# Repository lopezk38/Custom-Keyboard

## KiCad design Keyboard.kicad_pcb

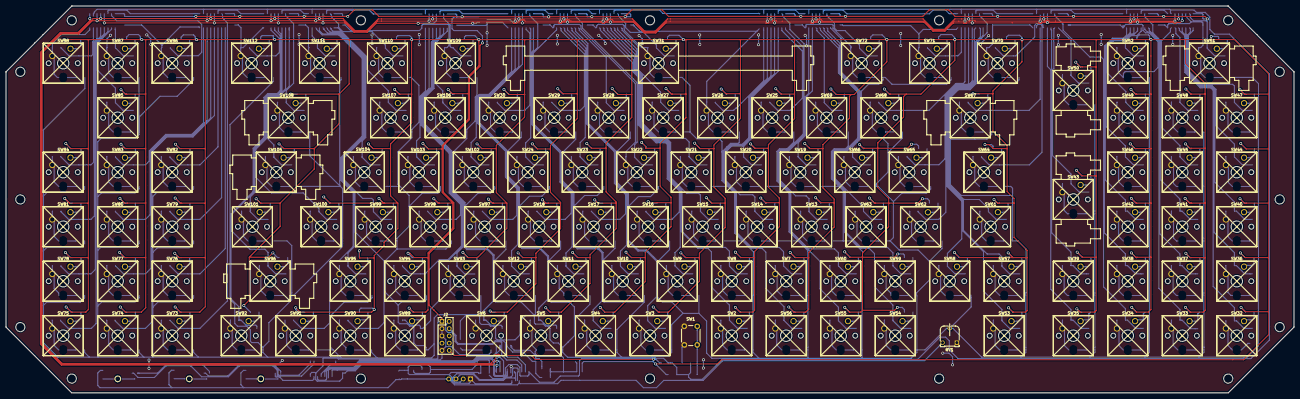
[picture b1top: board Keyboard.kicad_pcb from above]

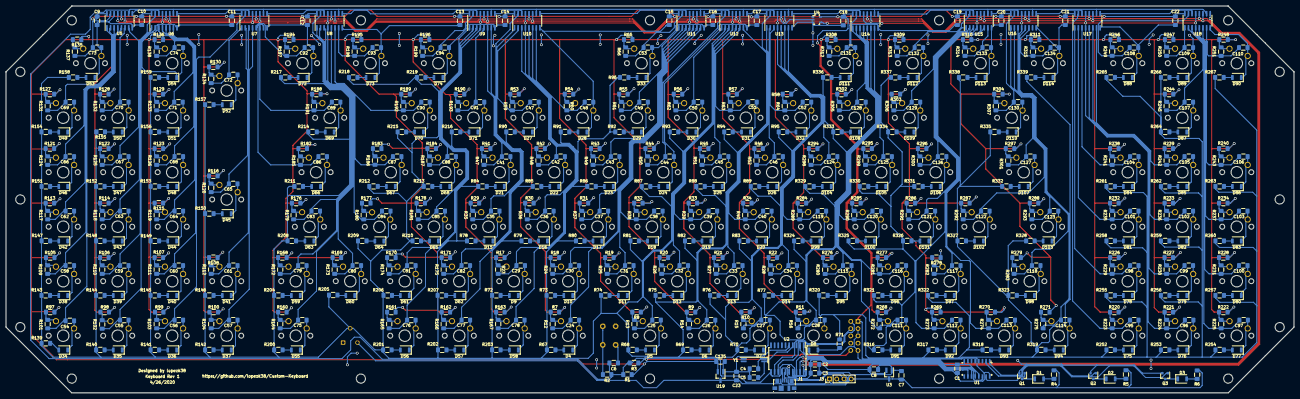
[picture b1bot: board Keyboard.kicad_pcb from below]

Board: 2 copper layers, 450.2 x 135.2 mm, 727 parts (613 on the bottom side), 375 nets.

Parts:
C1, C3: 100n; C_1206_3216Metric_Pad1.42x1.75mm_HandSolder
C2: 4.7u; C_1206_3216Metric_Pad1.42x1.75mm_HandSolder
C4, C5: 8.2p; C_1206_3216Metric_Pad1.42x1.75mm_HandSolder
C6: 4.7n; C_1206_3216Metric_Pad1.42x1.75mm_HandSolder
C7, C8, C23, C135: 1u; C_1206_3216Metric_Pad1.42x1.75mm_HandSolder
C9, C10, C11, C12, C13, C14, C15, C16, C17, C18, C19, C20, C21, C22: 1n; C_1206_3216Metric_Pad1.42x1.75mm_HandSolder
C24, C25, C26, C27, C28, C29, C30, C31, C32, C33, C34, C35, C36, C37, C38, C39, C40, C41, C42, C43, C44, C45, C46, C47, C48, C49, C50, C51, C52, C53, C54, C55, C56, C57, C58, C59, C60, C61, C62, C63, C64, C65, C66, C67, C68, C69, C70, C71, C72, C73, C74, C75, C76, C77, C78, C79, C80, C81, C82, C83, C84, C85, C86, C87, C88, C89, C90, C91, C92, C93, C94, C95, C96, C97, C98, C99, C100, C101, C102, C103, C104, C105, C106, C107, C108, C109, C110, C111, C112, C113, C114, C115, C116, C117, C118, C119, C120, C121, C122, C123, C124, C125, C126, C127, C128, C129, C130, C131, C132, C133, C134: .047u; C_1206_3216Metric_Pad1.42x1.75mm_HandSolder
D1: NUM LOCK; LED_1206_3216Metric_ReverseMount_Hole1.8x2.4mm
D2: CAPS LOCK; LED_1206_3216Metric_ReverseMount_Hole1.8x2.4mm
D3: SCROLL LOCK; LED_1206_3216Metric_ReverseMount_Hole1.8x2.4mm
D4: LED F4; LED_1206_3216Metric_ReverseMount_Hole1.8x2.4mm
D5: LED F5; LED_1206_3216Metric_ReverseMount_Hole1.8x2.4mm
D6: LED F6; LED_1206_3216Metric_ReverseMount_Hole1.8x2.4mm
D7: LED F7; LED_1206_3216Metric_ReverseMount_Hole1.8x2.4mm
D8: LED F8; LED_1206_3216Metric_ReverseMount_Hole1.8x2.4mm
D9, D46: LED 4; LED_1206_3216Metric_ReverseMount_Hole1.8x2.4mm
D10, D47: LED 5; LED_1206_3216Metric_ReverseMount_Hole1.8x2.4mm
D11, D48: LED 6; LED_1206_3216Metric_ReverseMount_Hole1.8x2.4mm
D12, D42: LED 7; LED_1206_3216Metric_ReverseMount_Hole1.8x2.4mm
D13, D43: LED 8; LED_1206_3216Metric_ReverseMount_Hole1.8x2.4mm
D14, D44: LED 9; LED_1206_3216Metric_ReverseMount_Hole1.8x2.4mm
D15: LED E; LED_1206_3216Metric_ReverseMount_Hole1.8x2.4mm
D16: LED R; LED_1206_3216Metric_ReverseMount_Hole1.8x2.4mm
D17: LED T; LED_1206_3216Metric_ReverseMount_Hole1.8x2.4mm
D18: LED Y; LED_1206_3216Metric_ReverseMount_Hole1.8x2.4mm
D19: LED U; LED_1206_3216Metric_ReverseMount_Hole1.8x2.4mm
D20: LED I; LED_1206_3216Metric_ReverseMount_Hole1.8x2.4mm
D21: LED D; LED_1206_3216Metric_ReverseMount_Hole1.8x2.4mm
D22: LED F; LED_1206_3216Metric_ReverseMount_Hole1.8x2.4mm
D23: LED G; LED_1206_3216Metric_ReverseMount_Hole1.8x2.4mm
D24: LED H; LED_1206_3216Metric_ReverseMount_Hole1.8x2.4mm
D25: LED J; LED_1206_3216Metric_ReverseMount_Hole1.8x2.4mm
D26: LED K; LED_1206_3216Metric_ReverseMount_Hole1.8x2.4mm
D27: LED C; LED_1206_3216Metric_ReverseMount_Hole1.8x2.4mm
D28: LED V; LED_1206_3216Metric_ReverseMount_Hole1.8x2.4mm
D29: LED B; LED_1206_3216Metric_ReverseMount_Hole1.8x2.4mm
D30: LED N; LED_1206_3216Metric_ReverseMount_Hole1.8x2.4mm
D31: LED M; LED_1206_3216Metric_ReverseMount_Hole1.8x2.4mm
D32: LED ,; LED_1206_3216Metric_ReverseMount_Hole1.8x2.4mm
D33: LED SPACE; LED_1206_3216Metric_ReverseMount_Hole1.8x2.4mm
D34: LED EXT1; LED_1206_3216Metric_ReverseMount_Hole1.8x2.4mm
D35: LED EXT2; LED_1206_3216Metric_ReverseMount_Hole1.8x2.4mm
D36: LED EXT3; LED_1206_3216Metric_ReverseMount_Hole1.8x2.4mm
D37: LED EXT4; LED_1206_3216Metric_ReverseMount_Hole1.8x2.4mm
D38: LED NUM LOCK; LED_1206_3216Metric_ReverseMount_Hole1.8x2.4mm
D39, D109: LED /; LED_1206_3216Metric_ReverseMount_Hole1.8x2.4mm
D40: LED *; LED_1206_3216Metric_ReverseMount_Hole1.8x2.4mm
D41, D96: LED -; LED_1206_3216Metric_ReverseMount_Hole1.8x2.4mm
D45: LED +; LED_1206_3216Metric_ReverseMount_Hole1.8x2.4mm
D49, D60: LED 1; LED_1206_3216Metric_ReverseMount_Hole1.8x2.4mm
D50, D61: LED 2; LED_1206_3216Metric_ReverseMount_Hole1.8x2.4mm
D51, D62: LED 3; LED_1206_3216Metric_ReverseMount_Hole1.8x2.4mm
D52, D107: LED ENTER; LED_1206_3216Metric_ReverseMount_Hole1.8x2.4mm
D53, D95: LED 0; LED_1206_3216Metric_ReverseMount_Hole1.8x2.4mm
D54, D108: LED .; LED_1206_3216Metric_ReverseMount_Hole1.8x2.4mm
D55: LED ESC; LED_1206_3216Metric_ReverseMount_Hole1.8x2.4mm
D56: LED F1; LED_1206_3216Metric_ReverseMount_Hole1.8x2.4mm
D57: LED F2; LED_1206_3216Metric_ReverseMount_Hole1.8x2.4mm
D58: LED F3; LED_1206_3216Metric_ReverseMount_Hole1.8x2.4mm
D59: LED `; LED_1206_3216Metric_ReverseMount_Hole1.8x2.4mm
D63: LED TAB; LED_1206_3216Metric_ReverseMount_Hole1.8x2.4mm
D64: LED Q; LED_1206_3216Metric_ReverseMount_Hole1.8x2.4mm
D65: LED W; LED_1206_3216Metric_ReverseMount_Hole1.8x2.4mm
D66: LED CAPL; LED_1206_3216Metric_ReverseMount_Hole1.8x2.4mm
D67: LED A; LED_1206_3216Metric_ReverseMount_Hole1.8x2.4mm
D68: LED S; LED_1206_3216Metric_ReverseMount_Hole1.8x2.4mm
D69: LED LSHFT; LED_1206_3216Metric_ReverseMount_Hole1.8x2.4mm
D70: LED Z; LED_1206_3216Metric_ReverseMount_Hole1.8x2.4mm
D71: LED X; LED_1206_3216Metric_ReverseMount_Hole1.8x2.4mm
D72: LED LCTRL; LED_1206_3216Metric_ReverseMount_Hole1.8x2.4mm
D73: LED LWIND; LED_1206_3216Metric_ReverseMount_Hole1.8x2.4mm
D74: LALT; LED_1206_3216Metric_ReverseMount_Hole1.8x2.4mm
D75: LED PRINT SCREEN; LED_1206_3216Metric_ReverseMount_Hole1.8x2.4mm
D76: LED SCROLL LOCK; LED_1206_3216Metric_ReverseMount_Hole1.8x2.4mm
D77: LED PAUSE; LED_1206_3216Metric_ReverseMount_Hole1.8x2.4mm
D78: LED INSERT; LED_1206_3216Metric_ReverseMount_Hole1.8x2.4mm
D79: LED HOME; LED_1206_3216Metric_ReverseMount_Hole1.8x2.4mm
D80: LED PAGE UP; LED_1206_3216Metric_ReverseMount_Hole1.8x2.4mm
D81: LED DELETE; LED_1206_3216Metric_ReverseMount_Hole1.8x2.4mm
D82: LED END; LED_1206_3216Metric_ReverseMount_Hole1.8x2.4mm
D83: LED PAGE DOWN; LED_1206_3216Metric_ReverseMount_Hole1.8x2.4mm
D84: LED EXT8; LED_1206_3216Metric_ReverseMount_Hole1.8x2.4mm
D85: LED EXT9; LED_1206_3216Metric_ReverseMount_Hole1.8x2.4mm
D86: LED EXT10; LED_1206_3216Metric_ReverseMount_Hole1.8x2.4mm
D87: LED UP; LED_1206_3216Metric_ReverseMount_Hole1.8x2.4mm
D88: LED LEFT; LED_1206_3216Metric_ReverseMount_Hole1.8x2.4mm
D89: LED DOWN; LED_1206_3216Metric_ReverseMount_Hole1.8x2.4mm
D90: LED RIGHT; LED_1206_3216Metric_ReverseMount_Hole1.8x2.4mm
D91: LED F9; LED_1206_3216Metric_ReverseMount_Hole1.8x2.4mm
D92: LED F10; LED_1206_3216Metric_ReverseMount_Hole1.8x2.4mm
D93: LED F11; LED_1206_3216Metric_ReverseMount_Hole1.8x2.4mm
D94: LED F12; LED_1206_3216Metric_ReverseMount_Hole1.8x2.4mm
D97: LED =; LED_1206_3216Metric_ReverseMount_Hole1.8x2.4mm
D98: LED BACK; LED_1206_3216Metric_ReverseMount_Hole1.8x2.4mm
D99: LED O; LED_1206_3216Metric_ReverseMount_Hole1.8x2.4mm
D100: LED P; LED_1206_3216Metric_ReverseMount_Hole1.8x2.4mm
D101: LED [; LED_1206_3216Metric_ReverseMount_Hole1.8x2.4mm
D102: LED ]; LED_1206_3216Metric_ReverseMount_Hole1.8x2.4mm
D103: LED \; LED_1206_3216Metric_ReverseMount_Hole1.8x2.4mm
D104: LED L; LED_1206_3216Metric_ReverseMount_Hole1.8x2.4mm
D105: LED ;; LED_1206_3216Metric_ReverseMount_Hole1.8x2.4mm
D106: LED '; LED_1206_3216Metric_ReverseMount_Hole1.8x2.4mm
D110: LED RSHIFT; LED_1206_3216Metric_ReverseMount_Hole1.8x2.4mm
D111: LED RALT; LED_1206_3216Metric_ReverseMount_Hole1.8x2.4mm
D112: LED RWIND; LED_1206_3216Metric_ReverseMount_Hole1.8x2.4mm
D113: LED APP; LED_1206_3216Metric_ReverseMount_Hole1.8x2.4mm
D114: LED RCTRL; LED_1206_3216Metric_ReverseMount_Hole1.8x2.4mm
J1: USB_B_Micro; USB_Micro-B_Molex_47346-0001
J2: DEBUG; PinHeader_2x05_P2.54mm_Vertical
J3: USB; PinHeader_1x04_P2.54mm_Vertical
Q1, Q2, Q3: DMG2302U; SOT-23
R1: 100K; R_1206_3216Metric_Pad1.42x1.75mm_HandSolder
R2, R3: 39; R_1206_3216Metric_Pad1.42x1.75mm_HandSolder
R4, R5, R6, R67, R68, R69, R70, R71, R72, R73, R74, R75, R76, R77, R78, R79, R80, R81, R82, R83, R84, R85, R86, R87, R88, R89, R90, R91, R92, R93, R94, R95, R96, R139, R140, R141, R142, R143, R144, R145, R146, R147, R148, R149, R150, R151, R152, R153, R154, R155, R156, R157, R158, R159, R200, R201, R202, R203, R204, R205, R206, R207, R208, R209, R210, R211, R212, R213, R214, R215, R216, R217, R218, R219, R252, R253, R254, R255, R256, R257, R258, R259, R260, R261, R262, R263, R264, R265, R266, R267, R316, R317, R318, R319, R320, R321, R322, R323, R324, R325, R326, R327, R328, R329, R330, R331, R332, R333, R334, R335, R336, R337, R338, R339: 1.8k; R_1206_3216Metric_Pad1.42x1.75mm_HandSolder
R7, R8, R9, R10, R11, R12, R13, R14, R15, R16, R17, R18, R19, R20, R21, R22, R23, R24, R25, R26, R27, R28, R29, R30, R31, R32, R33, R34, R35, R36, R37, R38, R39, R40, R41, R42, R43, R44, R45, R46, R47, R48, R49, R50, R51, R52, R53, R54, R55, R56, R57, R58, R59, R60, R61, R62, R63, R64, R65, R66, R97, R98, R99, R100, R101, R102, R103, R104, R105, R106, R107, R108, R109, R110, R111, R112, R113, R114, R115, R116, R117, R118, R119, R120, R121, R122, R123, R124, R125, R126, R127, R128, R129, R130, R131, R132, R133, R134, R135, R136, R137, R138, R160, R161, R162, R163, R164, R165, R166, R167, R168, R169, R170, R171, R172, R173, R174, R175, R176, R177, R178, R179, R180, R181, R182, R183, R184, R185, R186, R187, R188, R189, R190, R191, R192, R193, R194, R195, R196, R197, R198, R199, R220, R221, R222, R223, R224, R225, R226, R227, R228, R229, R230, R231, R232, R233, R234, R235, R236, R237, R238, R239, R240, R241, R242, R243, R244, R245, R246, R247, R248, R249, R250, R251, R268, R269, R270, R271, R272, R273, R274, R275, R276, R277, R278, R279, R280, R281, R282, R283, R284, R285, R286, R287, R288, R289, R290, R291, R292, R293, R294, R295, R296, R297, R298, R299, R300, R301, R302, R303, R304, R305, R306, R307, R308, R309, R310, R311, R312, R313, R314, R315: 10k; R_1206_3216Metric_Pad1.42x1.75mm_HandSolder
RV1: R_POT; Potentiometer_Runtron_RM-065_Vertical
SW1: SW_Push; SW_PUSH_6mm
SW2: F4; SW_Cherry_MX_1.00u_PCB
SW3: F5; SW_Cherry_MX_1.00u_PCB
SW4: F6; SW_Cherry_MX_1.00u_PCB
SW5: F7; SW_Cherry_MX_1.00u_PCB
SW6: F8; SW_Cherry_MX_1.00u_PCB
SW7, SW44: 4; SW_Cherry_MX_1.00u_PCB
SW8, SW45: 5; SW_Cherry_MX_1.00u_PCB
SW9, SW46: 6; SW_Cherry_MX_1.00u_PCB
SW10, SW40: 7; SW_Cherry_MX_1.00u_PCB
SW11, SW41: 8; SW_Cherry_MX_1.00u_PCB
SW12, SW42: 9; SW_Cherry_MX_1.00u_PCB
SW13: E; SW_Cherry_MX_1.00u_PCB
SW14: R; SW_Cherry_MX_1.00u_PCB
SW15: T; SW_Cherry_MX_1.00u_PCB
SW16: Y; SW_Cherry_MX_1.00u_PCB
SW17: U; SW_Cherry_MX_1.00u_PCB
SW18: I; SW_Cherry_MX_1.00u_PCB
SW19: D; SW_Cherry_MX_1.00u_PCB
SW20: F; SW_Cherry_MX_1.00u_PCB
SW21: G; SW_Cherry_MX_1.00u_PCB
SW22: H; SW_Cherry_MX_1.00u_PCB
SW23: J; SW_Cherry_MX_1.00u_PCB
SW24: K; SW_Cherry_MX_1.00u_PCB
SW25: C; SW_Cherry_MX_1.00u_PCB
SW26: V; SW_Cherry_MX_1.00u_PCB
SW27: B; SW_Cherry_MX_1.00u_PCB
SW28: N; SW_Cherry_MX_1.00u_PCB
SW29: M; SW_Cherry_MX_1.00u_PCB
SW30: ,; SW_Cherry_MX_1.00u_PCB
SW31: SPACE; SW_Cherry_MX_1.00u_PCB
SW32: EXT1; SW_Cherry_MX_1.00u_PCB
SW33: EXT2; SW_Cherry_MX_1.00u_PCB
SW34: EXT3; SW_Cherry_MX_1.00u_PCB
SW35: EXT4; SW_Cherry_MX_1.00u_PCB
SW36: NUM LOCK; SW_Cherry_MX_1.00u_PCB
SW37, SW107: /; SW_Cherry_MX_1.00u_PCB
SW38: *; SW_Cherry_MX_1.00u_PCB
SW39, SW94: -; SW_Cherry_MX_1.00u_PCB
SW43: +; SW_Cherry_MX_1.00u_PCB
SW47, SW58: 1; SW_Cherry_MX_1.00u_PCB
SW48, SW59: 2; SW_Cherry_MX_1.00u_PCB
SW49, SW60: 3; SW_Cherry_MX_1.00u_PCB
SW50, SW105: ENTER; SW_Cherry_MX_1.00u_PCB
SW51, SW93: 0; SW_Cherry_MX_1.00u_PCB
SW52, SW106: .; SW_Cherry_MX_1.00u_PCB
SW53: ESC; SW_Cherry_MX_1.00u_PCB
SW54: F1; SW_Cherry_MX_1.00u_PCB
SW55: F2; SW_Cherry_MX_1.00u_PCB
SW56: F3; SW_Cherry_MX_1.00u_PCB
SW57: `; SW_Cherry_MX_1.00u_PCB
SW61: TAB; SW_Cherry_MX_1.00u_PCB
SW62: Q; SW_Cherry_MX_1.00u_PCB
SW63: W; SW_Cherry_MX_1.00u_PCB
SW64: CAPL; SW_Cherry_MX_1.00u_PCB
SW65: A; SW_Cherry_MX_1.00u_PCB
SW66: S; SW_Cherry_MX_1.00u_PCB
SW67: LSHFT; SW_Cherry_MX_1.00u_PCB
SW68: Z; SW_Cherry_MX_1.00u_PCB
SW69: X; SW_Cherry_MX_1.00u_PCB
SW70: LCTRL; SW_Cherry_MX_1.00u_PCB
SW71: LWIND; SW_Cherry_MX_1.00u_PCB
SW72: LALT; SW_Cherry_MX_1.00u_PCB
SW73: PRINT SCREEN; SW_Cherry_MX_1.00u_PCB
SW74: SCRL; SW_Cherry_MX_1.00u_PCB
SW75: PAUSE; SW_Cherry_MX_1.00u_PCB
SW76: INSERT; SW_Cherry_MX_1.00u_PCB
SW77: HOME; SW_Cherry_MX_1.00u_PCB
SW78: PAGE UP; SW_Cherry_MX_1.00u_PCB
SW79: DELETE; SW_Cherry_MX_1.00u_PCB
SW80: END; SW_Cherry_MX_1.00u_PCB
SW81: PAGE DOWN; SW_Cherry_MX_1.00u_PCB
SW82: EXT8; SW_Cherry_MX_1.00u_PCB
SW83: EXT9; SW_Cherry_MX_1.00u_PCB
SW84: EXT10; SW_Cherry_MX_1.00u_PCB
SW85: UP; SW_Cherry_MX_1.00u_PCB
SW86: LEFT; SW_Cherry_MX_1.00u_PCB
SW87: DOWN; SW_Cherry_MX_1.00u_PCB
SW88: RIGHT; SW_Cherry_MX_1.00u_PCB
SW89: F9; SW_Cherry_MX_1.00u_PCB
SW90: F10; SW_Cherry_MX_1.00u_PCB
SW91: F11; SW_Cherry_MX_1.00u_PCB
SW92: F12; SW_Cherry_MX_1.00u_PCB
SW95: =; SW_Cherry_MX_1.00u_PCB
SW96: BACKSPACE; SW_Cherry_MX_1.00u_PCB
SW97: O; SW_Cherry_MX_1.00u_PCB
SW98: P; SW_Cherry_MX_1.00u_PCB
SW99: [; SW_Cherry_MX_1.00u_PCB
SW100: ]; SW_Cherry_MX_1.00u_PCB
SW101: \; SW_Cherry_MX_1.00u_PCB
SW102: L; SW_Cherry_MX_1.00u_PCB
SW103: ;; SW_Cherry_MX_1.00u_PCB
SW104: '; SW_Cherry_MX_1.00u_PCB
SW108: RSHFT; SW_Cherry_MX_1.00u_PCB
SW109: RALT; SW_Cherry_MX_1.00u_PCB
SW110: RWIND; SW_Cherry_MX_1.00u_PCB
SW111: APP; SW_Cherry_MX_1.00u_PCB
SW112: RCTRL; SW_Cherry_MX_1.00u_PCB
U1: 74HC595D_118; SOIC-16_W3.90mm
U2: ATSAMD11D14A-SS; SOIC-20W_7.5x12.8mm_P1.27mm
U3, U19: AP2138N-3.3TRG1; SOT-23_Handsoldering
U4: SN74LVC1G04DBVR; SOT-753
U5, U6, U7, U8, U9, U10, U11, U12, U13, U14, U15, U16, U17, U18: 74LS597; SOIC-16_3.9x9.9mm_P1.27mm
Y1: Crystal_GND2; Crystal_SMD_SeikoEpson_MC146-4Pin_6.7x1.5mm_HandSoldering

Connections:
+3V3: C1.1, C2.1, C3.1, C8.1, C9.1, C10.1, C11.1, C12.1, C13.1, C14.1, C15.1, C16.1, C17.1, C18.1, C19.1, C20.1, C21.1, C22.1, J2.1, U1.16, U2.17, U3.2, U4.5, U5.16, U6.16, U7.16, U8.16, U9.16, U10.16, U11.16, U12.16, U13.16, U14.16, U15.16, U16.16, U17.16, U18.16
+5V: C7.1, C23.1, J1.1, J3.4, R4.2, R5.2, R6.2, RV1.3, U3.3, U19.3
/CMK/0: C115.2, R280.2, U14.3
/CMK/1: C80.2, R173.2, U8.3
/CMK/2: C81.2, R174.2, U9.3
/CMK/3: C82.2, R175.2, U10.15
/CMK/3.3V_SWITCHES: C135.1, R1.1, R7.1, R8.1, R9.1, R10.1, R11.1, R17.1, R18.1, R19.1, R20.1, R21.1, R22.1, R29.1, R30.1, R31.1, R32.1, R33.1, R34.1, R41.1, R42.1, R43.1, R44.1, R45.1, R46.1, R53.1, R54.1, R55.1, R56.1, R57.1, R58.1, R65.1, R97.1, R98.1, R99.1, R100.1, R105.1, R106.1, R107.1, R108.1, R113.1, R114.1, R115.1, R116.1, R121.1, R122.1, R123.1, R127.1, R128.1, R129.1, R130.1, R135.1, R136.1, R160.1, R161.1, R162.1, R163.1, R168.1, R169.1, R170.1, R171.1, R176.1, R177.1, R178.1, R182.1, R183.1, R184.1, R188.1, R189.1, R190.1, R194.1, R195.1, R196.1, R220.1, R221.1, R222.1, R226.1, R227.1, R228.1, R232.1, R233.1, R234.1, R238.1, R239.1, R240.1, R244.1, R246.1, R247.1, R248.1, R268.1, R269.1, R270.1, R271.1, R276.1, R277.1, R278.1, R279.1, R284.1, R285.1, R286.1, R287.1, R288.1, R294.1, R295.1, R296.1, R297.1, R302.1, R303.1, R304.1, R308.1, R309.1, R310.1, R311.1, U19.2
/CMK/4: C29.2, R23.2, U10.5
/CMK/5: C30.2, R24.2, U11.4
/CMK/6: C31.2, R25.2, U11.6
/CMK/7: C32.2, R26.2, U12.3
/CMK/8: C33.2, R27.2, U13.15
/CMK/9: C34.2, R28.2, U13.5
/CMK/': C126.2, R300.2, U15.2
/CMK/,: C52.2, R64.2, U13.3
/CMK/-: C116.2, R281.2, U14.5
/CMK/.: C128.2, R305.2, U14.1
/CMK/;: C125.2, R299.2, U14.7
/CMK/=: C117.2, R282.2, U15.5
/CMK/A: C87.2, R186.2, U8.5
/CMK/APP: C133.2, R314.2, U15.7
/CMK/B: C49.2, R61.2, U11.1
/CMK/BACK: C118.2, R283.2, U16.4
/CMK/C: C47.2, R59.2, U10.2
/CMK/CAPL: C86.2, R185.2, U7.7
/CMK/D: C41.2, R47.2, U9.6
/CMK/DEL: C101.2, R235.2, U17.2
/CMK/DIMMER: R67.2, R68.2, R69.2, R70.2, R71.2, R72.2, R73.2, R74.2, R75.2, R76.2, R77.2, R78.2, R79.2, R80.2, R81.2, R82.2, R83.2, R84.2, R85.2, R86.2, R87.2, R88.2, R89.2, R90.2, R91.2, R92.2, R93.2, R94.2, R95.2, R96.2, R139.2, R140.2, R141.2, R142.2, R143.2, R144.2, R145.2, R146.2, R147.2, R148.2, R149.2, R150.2, R151.2, R152.2, R153.2, R154.2, R155.2, R156.2, R157.2, R158.2, R159.2, R200.2, R201.2, R202.2, R203.2, R204.2, R205.2, R206.2, R207.2, R208.2, R209.2, R210.2, R211.2, R212.2, R213.2, R214.2, R215.2, R216.2, R217.2, R218.2, R219.2, R252.2, R253.2, R254.2, R255.2, R256.2, R257.2, R258.2, R259.2, R260.2, R261.2, R262.2, R263.2, R264.2, R265.2, R266.2, R267.2, R316.2, R317.2, R318.2, R319.2, R320.2, R321.2, R322.2, R323.2, R324.2, R325.2, R326.2, R327.2, R328.2, R329.2, R330.2, R331.2, R332.2, R333.2, R334.2, R335.2, R336.2, R337.2, R338.2, R339.2, RV1.2
/CMK/DN: C109.2, R250.2, U18.1
/CMK/E: C35.2, R35.2, U9.7
/CMK/END: C102.2, R236.2, U17.6
/CMK/ENTER: C127.2, R301.2, U16.1
/CMK/ESC: C75.2, R164.2, U8.2
/CMK/EXT1: C54.2, R101.2, U5.5
/CMK/EXT2: C55.2, R102.2, U6.2
/CMK/EXT3: C56.2, R103.2, U7.15
/CMK/EXT4: C57.2, R104.2, U7.4
/CMK/EXT8: C104.2, R241.2, U17.3
/CMK/EXT9: C105.2, R242.2, U17.7
/CMK/EXT10: C106.2, R243.2, U18.6
/CMK/F: C42.2, R48.2, U10.3
/CMK/F1: C76.2, R165.2, U9.4
/CMK/F2: C77.2, R166.2, U10.1
/CMK/F3: C78.2, R167.2, U10.6
/CMK/F4: C24.2, R12.2, U11.5
/CMK/F5: C25.2, R13.2, U12.2
/CMK/F6: C26.2, R14.2, U12.7
/CMK/F7: C27.2, R15.2, U13.4
/CMK/F8: C28.2, R16.2, U14.2
/CMK/F9: C111.2, R272.2, U14.4
/CMK/F10: C112.2, R273.2, U15.4
/CMK/F11: C113.2, R274.2, U15.6
/CMK/F12: C114.2, R275.2, U16.5
/CMK/G: C43.2, R49.2, U11.2
/CMK/H: C44.2, R50.2, U12.15
/CMK/HOME: C99.2, R230.2, U17.5
/CMK/I: C40.2, R40.2, U13.1
/CMK/INS: C98.2, R229.2, U17.1
/CMK/J: C45.2, R51.2, U12.5
/CMK/K: C46.2, R52.2, U13.2
/CMK/L: C124.2, R298.2, U13.7
/CMK/LALT: C94.2, R199.2, U9.15
/CMK/LCTRL: C92.2, R197.2, U7.5
/CMK/LSHFT: C89.2, R191.2, U7.6
/CMK/LT: C108.2, R249.2, U18.15
/CMK/LWIND: C93.2, R198.2, U8.7
/CMK/M: C51.2, R63.2, U12.6
/CMK/N: C50.2, R62.2, U12.1
/CMK/NUM0: C73.2, R137.2, U5.15
/CMK/NUM1: C69.2, R131.2, U5.1
/CMK/NUM2: C70.2, R132.2, U5.6
/CMK/NUM3: C71.2, R133.2, U6.4
/CMK/NUM4: C66.2, R124.2, U5.2
/CMK/NUM5: C67.2, R125.2, U5.7
/CMK/NUM6: C68.2, R126.2, U6.5
/CMK/NUM7: C62.2, R117.2, U5.3
/CMK/NUM8: C63.2, R118.2, U6.15
/CMK/NUM9: C64.2, R119.2, U6.6
/CMK/NUM*: C60.2, R111.2, U6.7
/CMK/NUM+: C65.2, R120.2, U7.2
/CMK/NUM-: C61.2, R112.2, U7.3
/CMK/NUM.: C74.2, R138.2, U6.3
/CMK/NUME: C72.2, R134.2, U7.1
/CMK/NUML: C58.2, R109.2, U5.4
/CMK/NUMS: C59.2, R110.2, U6.1
/CMK/O: C119.2, R289.2, U13.6
/CMK/P: C120.2, R290.2, U14.6
/CMK/PAUS: C97.2, R225.2, U18.3
/CMK/PGDN: C103.2, R237.2, U18.5
/CMK/PGUP: C100.2, R231.2, U18.4
/CMK/PRNT: C95.2, R223.2, U17.15
/CMK/Q: C84.2, R180.2, U8.4
/CMK/R: C36.2, R36.2, U10.4
/CMK/RALT: C131.2, R312.2, U14.15
/CMK/RCTRL: C134.2, R315.2, U16.6
/CMK/RESET: C6.1, R1.2, R2.2, R3.1, U1.10, U2.11, U5.10, U6.10, U7.10, U8.10, U9.10, U10.10, U11.10, U12.10, U13.10, U14.10, U15.10, U16.10, U17.10, U18.10
/CMK/RSHFT: C130.2, R307.2, U16.15
/CMK/RT: C110.2, R251.2, U18.7
/CMK/RWIND: C132.2, R313.2, U15.15
/CMK/S: C88.2, R187.2, U9.1
/CMK/SCRL: C96.2, R224.2, U17.4
/CMK/SHIFT_CLK: U1.11, U2.18, U5.11, U6.11, U7.11, U8.11, U9.11, U10.11, U11.11, U12.11, U13.11, U14.11, U15.11, U16.11, U17.11, U18.11
/CMK/SHIFT_DATA: U2.20, U18.9
/CMK/SHIFT_RCLK: U2.19, U4.2, U5.12, U6.12, U7.12, U8.12, U9.12, U10.12, U11.12, U12.12, U13.12, U14.12, U15.12, U16.12, U17.12, U18.12
/CMK/SLSH: C129.2, R306.2, U15.1
/CMK/SP: C53.2, R66.2, U11.15
/CMK/T: C37.2, R37.2, U11.3
/CMK/TAB: C83.2, R179.2, U8.15
/CMK/U: C39.2, R39.2, U12.4
/CMK/UP: C107.2, R245.2, U18.2
/CMK/V: C48.2, R60.2, U10.7
/CMK/W: C85.2, R181.2, U9.2
/CMK/X: C91.2, R193.2, U9.5
/CMK/Y: C38.2, R38.2, U11.7
/CMK/Z: C90.2, R192.2, U8.6
/CMK/[: C121.2, R291.2, U15.3
/CMK/\: C123.2, R293.2, U16.3
/CMK/]: C122.2, R292.2, U16.2
/CMK/`: C79.2, R172.2, U8.1
/Controller Sheet/Lock LEDS/CAPS_LOCK: Q2.1, U1.1
/Controller Sheet/Lock LEDS/NUM_LOCK: Q1.1, U1.15
/Controller Sheet/Lock LEDS/SCROLL_LOCK: Q3.1, U1.2
/Controller Sheet/OUT_SHIFT_0_DATA: U1.14, U2.2
/Controller Sheet/OUT_SHIFT_RCLK: U1.12, U2.1
/Controller Sheet/RESET_DBG: J2.10, R3.2
/Controller Sheet/SWCLK: J2.4, U2.12
/Controller Sheet/SWDIO: J2.2, U2.13
/Controller Sheet/USB_N: J1.2, J3.2, U2.14
/Controller Sheet/USB_P: J1.3, J3.3, U2.15
GND: C1.2, C2.2, C3.2, C4.2, C5.2, C6.2, C7.2, C8.2, C9.2, C10.2, C11.2, C12.2, C13.2, C14.2, C15.2, C16.2, C17.2, C18.2, C19.2, C20.2, C21.2, C22.2, C23.2, C24.1, C25.1, C26.1, C27.1, C28.1, C29.1, C30.1, C31.1, C32.1, C33.1, C34.1, C35.1, C36.1, C37.1, C38.1, C39.1, C40.1, C41.1, C42.1, C43.1, C44.1, C45.1, C46.1, C47.1, C48.1, C49.1, C50.1, C51.1, C52.1, C53.1, C54.1, C55.1, C56.1, C57.1, C58.1, C59.1, C60.1, C61.1, C62.1, C63.1, C64.1, C65.1, C66.1, C67.1, C68.1, C69.1, C70.1, C71.1, C72.1, C73.1, C74.1, C75.1, C76.1, C77.1, C78.1, C79.1, C80.1, C81.1, C82.1, C83.1, C84.1, C85.1, C86.1, C87.1, C88.1, C89.1, C90.1, C91.1, C92.1, C93.1, C94.1, C95.1, C96.1, C97.1, C98.1, C99.1, C100.1, C101.1, C102.1, C103.1, C104.1, C105.1, C106.1, C107.1, C108.1, C109.1, C110.1, C111.1, C112.1, C113.1, C114.1, C115.1, C116.1, C117.1, C118.1, C119.1, C120.1, C121.1, C122.1, C123.1, C124.1, C125.1, C126.1, C127.1, C128.1, C129.1, C130.1, C131.1, C132.1, C133.1, C134.1, C135.2, D4.1, D5.1, D6.1, D7.1, D8.1, D9.1, D10.1, D11.1, D12.1, D13.1, D14.1, D15.1, D16.1, D17.1, D18.1, D19.1, D20.1, D21.1, D22.1, D23.1, D24.1, D25.1, D26.1, D27.1, D28.1, D29.1, D30.1, D31.1, D32.1, D33.1, D34.1, D35.1, D36.1, D37.1, D38.1, D39.1, D40.1, D41.1, D42.1, D43.1, D44.1, D45.1, D46.1, D47.1, D48.1, D49.1, D50.1, D51.1, D52.1, D53.1, D54.1, D55.1, D56.1, D57.1, D58.1, D59.1, D60.1, D61.1, D62.1, D63.1, D64.1, D65.1, D66.1, D67.1, D68.1, D69.1, D70.1, D71.1, D72.1, D73.1, D74.1, D75.1, D76.1, D77.1, D78.1, D79.1, D80.1, D81.1, D82.1, D83.1, D84.1, D85.1, D86.1, D87.1, D88.1, D89.1, D90.1, D91.1, D92.1, D93.1, D94.1, D95.1, D96.1, D97.1, D98.1, D99.1, D100.1, D101.1, D102.1, D103.1, D104.1, D105.1, D106.1, D107.1, D108.1, D109.1, D110.1, D111.1, D112.1, D113.1, D114.1, J1.5, J2.3, J2.5, J2.9, J3.1, Q1.2, Q2.2, Q3.2, RV1.1, SW1.2, SW2.2, SW3.2, SW4.2, SW5.2, SW6.2, SW7.2, SW8.2, SW9.2, SW10.2, SW11.2, SW12.2, SW13.2, SW14.2, SW15.2, SW16.2, SW17.2, SW18.2, SW19.2, SW20.2, SW21.2, SW22.2, SW23.2, SW24.2, SW25.2, SW26.2, SW27.2, SW28.2, SW29.2, SW30.2, SW31.2, SW32.2, SW33.2, SW34.2, SW35.2, SW36.2, SW37.2, SW38.2, SW39.2, SW40.2, SW41.2, SW42.2, SW43.2, SW44.2, SW45.2, SW46.2, SW47.2, SW48.2, SW49.2, SW50.2, SW51.2, SW52.2, SW53.2, SW54.2, SW55.2, SW56.2, SW57.2, SW58.2, SW59.2, SW60.2, SW61.2, SW62.2, SW63.2, SW64.2, SW65.2, SW66.2, SW67.2, SW68.2, SW69.2, SW70.2, SW71.2, SW72.2, SW73.2, SW74.2, SW75.2, SW76.2, SW77.2, SW78.2, SW79.2, SW80.2, SW81.2, SW82.2, SW83.2, SW84.2, SW85.2, SW86.2, SW87.2, SW88.2, SW89.2, SW90.2, SW91.2, SW92.2, SW93.2, SW94.2, SW95.2, SW96.2, SW97.2, SW98.2, SW99.2, SW100.2, SW101.2, SW102.2, SW103.2, SW104.2, SW105.2, SW106.2, SW107.2, SW108.2, SW109.2, SW110.2, SW111.2, SW112.2, U1.8, U1.13, U2.16, U3.1, U4.3, U5.8, U5.14, U6.8, U7.8, U8.8, U9.8, U10.8, U11.8, U12.8, U13.8, U14.8, U15.8, U16.8, U17.8, U18.8, U19.1
unnamed: C4.1, U2.5, Y1.1
unnamed: C5.1, U2.4, Y1.4
unnamed: D1.1, Q1.3
unnamed: D1.2, R4.1
unnamed: D2.1, Q2.3
unnamed: D2.2, R5.1
unnamed: D3.1, Q3.3
unnamed: D3.2, R6.1
unnamed: D4.2, R67.1
unnamed: D5.2, R68.1
unnamed: D6.2, R69.1
unnamed: D7.2, R70.1
unnamed: D8.2, R71.1
unnamed: D9.2, R72.1
unnamed: D10.2, R73.1
unnamed: D11.2, R74.1
unnamed: D12.2, R75.1
unnamed: D13.2, R76.1
unnamed: D14.2, R77.1
unnamed: D15.2, R78.1
unnamed: D16.2, R79.1
unnamed: D17.2, R80.1
unnamed: D18.2, R81.1
unnamed: D19.2, R82.1
unnamed: D20.2, R83.1
unnamed: D21.2, R84.1
unnamed: D22.2, R85.1
unnamed: D23.2, R86.1
unnamed: D24.2, R87.1
unnamed: D25.2, R88.1
unnamed: D26.2, R89.1
unnamed: D27.2, R90.1
unnamed: D28.2, R91.1
unnamed: D29.2, R92.1
unnamed: D30.2, R93.1
unnamed: D31.2, R94.1
unnamed: D32.2, R95.1
unnamed: D33.2, R96.1
unnamed: D34.2, R139.1
unnamed: D35.2, R140.1
unnamed: D36.2, R141.1
unnamed: D37.2, R142.1
unnamed: D38.2, R143.1
unnamed: D39.2, R144.1
unnamed: D40.2, R145.1
unnamed: D41.2, R146.1
unnamed: D42.2, R147.1
unnamed: D43.2, R148.1
unnamed: D44.2, R149.1
unnamed: D45.2, R150.1
unnamed: D46.2, R151.1
unnamed: D47.2, R152.1
unnamed: D48.2, R153.1
unnamed: D49.2, R154.1
unnamed: D50.2, R155.1
unnamed: D51.2, R156.1
unnamed: D52.2, R157.1
unnamed: D53.2, R158.1
unnamed: D54.2, R159.1
unnamed: D55.2, R200.1
unnamed: D56.2, R201.1
unnamed: D57.2, R202.1
unnamed: D58.2, R203.1
unnamed: D59.2, R204.1
unnamed: D60.2, R205.1
unnamed: D61.2, R206.1
unnamed: D62.2, R207.1
unnamed: D63.2, R208.1
unnamed: D64.2, R209.1
unnamed: D65.2, R210.1
unnamed: D66.2, R211.1
unnamed: D67.2, R212.1
unnamed: D68.2, R213.1
unnamed: D69.2, R214.1
unnamed: D70.2, R215.1
unnamed: D71.2, R216.1
unnamed: D72.2, R217.1
unnamed: D73.2, R218.1
unnamed: D74.2, R219.1
unnamed: D75.2, R252.1
unnamed: D76.2, R253.1
unnamed: D77.2, R254.1
unnamed: D78.2, R255.1
unnamed: D79.2, R256.1
unnamed: D80.2, R257.1
unnamed: D81.2, R258.1
unnamed: D82.2, R259.1
unnamed: D83.2, R260.1
unnamed: D84.2, R261.1
unnamed: D85.2, R262.1
unnamed: D86.2, R263.1
unnamed: D87.2, R264.1
unnamed: D88.2, R265.1
unnamed: D89.2, R266.1
unnamed: D90.2, R267.1
unnamed: D91.2, R316.1
unnamed: D92.2, R317.1
unnamed: D93.2, R318.1
unnamed: D94.2, R319.1
unnamed: D95.2, R320.1
unnamed: D96.2, R321.1
unnamed: D97.2, R322.1
unnamed: D98.2, R323.1
unnamed: D99.2, R324.1
unnamed: D100.2, R325.1
unnamed: D101.2, R326.1
unnamed: D102.2, R327.1
unnamed: D103.2, R328.1
unnamed: D104.2, R329.1
unnamed: D105.2, R330.1
unnamed: D106.2, R331.1
unnamed: D107.2, R332.1
unnamed: D108.2, R333.1
unnamed: D109.2, R334.1
unnamed: D110.2, R335.1
unnamed: D111.2, R336.1
unnamed: D112.2, R337.1
unnamed: D113.2, R338.1
unnamed: D114.2, R339.1
unnamed: R2.1, SW1.1
unnamed: R10.2, R15.1, SW5.1
unnamed: R11.2, R16.1, SW6.1
unnamed: R7.2, R12.1, SW2.1
unnamed: R8.2, R13.1, SW3.1
unnamed: R9.2, R14.1, SW4.1
unnamed: R17.2, R23.1, SW7.1
unnamed: R18.2, R24.1, SW8.1
unnamed: R19.2, R25.1, SW9.1
unnamed: R20.2, R26.1, SW10.1
unnamed: R21.2, R27.1, SW11.1
unnamed: R22.2, R28.1, SW12.1
unnamed: R29.2, R35.1, SW13.1
unnamed: R30.2, R36.1, SW14.1
unnamed: R31.2, R37.1, SW15.1
unnamed: R32.2, R38.1, SW16.1
unnamed: R33.2, R39.1, SW17.1
unnamed: R34.2, R40.1, SW18.1
unnamed: R41.2, R47.1, SW19.1
unnamed: R42.2, R48.1, SW20.1
unnamed: R43.2, R49.1, SW21.1
unnamed: R44.2, R50.1, SW22.1
unnamed: R45.2, R51.1, SW23.1
unnamed: R46.2, R52.1, SW24.1
unnamed: R53.2, R59.1, SW25.1
unnamed: R54.2, R60.1, SW26.1
unnamed: R55.2, R61.1, SW27.1
unnamed: R56.2, R62.1, SW28.1
unnamed: R57.2, R63.1, SW29.1
unnamed: R58.2, R64.1, SW30.1
unnamed: R65.2, R66.1, SW31.1
unnamed: R100.2, R104.1, SW35.1
unnamed: R97.2, R101.1, SW32.1
unnamed: R98.2, R102.1, SW33.1
unnamed: R99.2, R103.1, SW34.1
unnamed: R105.2, R109.1, SW36.1
unnamed: R106.2, R110.1, SW37.1
unnamed: R107.2, R111.1, SW38.1
unnamed: R108.2, R112.1, SW39.1
unnamed: R113.2, R117.1, SW40.1
unnamed: R114.2, R118.1, SW41.1
unnamed: R115.2, R119.1, SW42.1
unnamed: R116.2, R120.1, SW43.1
unnamed: R121.2, R124.1, SW44.1
unnamed: R122.2, R125.1, SW45.1
unnamed: R123.2, R126.1, SW46.1
unnamed: R127.2, R131.1, SW47.1
unnamed: R128.2, R132.1, SW48.1
unnamed: R129.2, R133.1, SW49.1
unnamed: R130.2, R134.1, SW50.1
unnamed: R135.2, R137.1, SW51.1
unnamed: R136.2, R138.1, SW52.1
unnamed: R160.2, R164.1, SW53.1
unnamed: R161.2, R165.1, SW54.1
unnamed: R162.2, R166.1, SW55.1
unnamed: R163.2, R167.1, SW56.1
unnamed: R168.2, R172.1, SW57.1
unnamed: R169.2, R173.1, SW58.1
unnamed: R170.2, R174.1, SW59.1
unnamed: R171.2, R175.1, SW60.1
unnamed: R176.2, R179.1, SW61.1
unnamed: R177.2, R180.1, SW62.1
unnamed: R178.2, R181.1, SW63.1
unnamed: R182.2, R185.1, SW64.1
unnamed: R183.2, R186.1, SW65.1
unnamed: R184.2, R187.1, SW66.1
unnamed: R188.2, R191.1, SW67.1
unnamed: R189.2, R192.1, SW68.1
unnamed: R190.2, R193.1, SW69.1
unnamed: R194.2, R197.1, SW70.1
unnamed: R195.2, R198.1, SW71.1
unnamed: R196.2, R199.1, SW72.1
unnamed: R220.2, R223.1, SW73.1
unnamed: R221.2, R224.1, SW74.1
unnamed: R222.2, R225.1, SW75.1
unnamed: R226.2, R229.1, SW76.1
unnamed: R227.2, R230.1, SW77.1
unnamed: R228.2, R231.1, SW78.1
unnamed: R232.2, R235.1, SW79.1
unnamed: R233.2, R236.1, SW80.1
unnamed: R234.2, R237.1, SW81.1
unnamed: R238.2, R241.1, SW82.1
unnamed: R239.2, R242.1, SW83.1
unnamed: R240.2, R243.1, SW84.1
unnamed: R244.2, R245.1, SW85.1
unnamed: R246.2, R249.1, SW86.1
unnamed: R247.2, R250.1, SW87.1
unnamed: R248.2, R251.1, SW88.1
unnamed: R268.2, R272.1, SW89.1
unnamed: R269.2, R273.1, SW90.1
unnamed: R270.2, R274.1, SW91.1
unnamed: R271.2, R275.1, SW92.1
unnamed: R276.2, R280.1, SW93.1
unnamed: R277.2, R281.1, SW94.1
unnamed: R278.2, R282.1, SW95.1
unnamed: R279.2, R283.1, SW96.1
unnamed: R284.2, R289.1, SW97.1
unnamed: R285.2, R290.1, SW98.1
unnamed: R286.2, R291.1, SW99.1
unnamed: R287.2, R292.1, SW100.1
unnamed: R288.2, R293.1, SW101.1
unnamed: R294.2, R298.1, SW102.1
unnamed: R295.2, R299.1, SW103.1
unnamed: R296.2, R300.1, SW104.1
unnamed: R297.2, R301.1, SW105.1
unnamed: R302.2, R305.1, SW106.1
unnamed: R303.2, R306.1, SW107.1
unnamed: R304.2, R307.1, SW108.1
unnamed: R308.2, R312.1, SW109.1
unnamed: R309.2, R313.1, SW110.1
unnamed: R310.2, R314.1, SW111.1
unnamed: R311.2, R315.1, SW112.1
unnamed: U5.9, U6.14
unnamed: U6.9, U7.14
unnamed: U7.9, U8.14
unnamed: U8.9, U9.14
unnamed: U10.9, U11.14
unnamed: U4.4, U5.13, U6.13, U7.13, U8.13, U9.13, U10.13, U11.13, U12.13, U13.13, U14.13, U15.13, U16.13, U17.13, U18.13
unnamed: U9.9, U10.14
unnamed: U11.9, U12.14
unnamed: U12.9, U13.14
unnamed: U13.9, U14.14
unnamed: U14.9, U15.14
unnamed: U15.9, U16.14
unnamed: U16.9, U17.14
unnamed: U17.9, U18.14

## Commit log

2020-04-07 Initial commit. Design NOT completed
2020-04-08 3 Board Schematics Complete
2020-04-11 Schematic completed first draft
2020-04-15 Fixed PISO Shift Register Wiring
2020-04-16 Corrected errors found in design rule check
2020-04-16 Fixed footprint for debug header
2020-04-17 Redesigned for single large PCB
2020-04-24 PCB Routed, minor circuit changes
2020-04-27 Generated Manufacturing Files, small PCB details
